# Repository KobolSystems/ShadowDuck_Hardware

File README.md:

# ShadowDuck Hardware

## DRAFT

<!-- Repo Cover Image -->

## Overview
The ShadowDuck is a hardware platform designed for performing keystroke injection attacks. Our goal with this platform is to provide a budget-friendly, educational, and ethical pen-testing tool that resembles a legitimate USB stick, avoiding unnecessary scrutiny. We aim to give newcomers to cybersecurity the opportunity to experiment with these tools and eventually apply their skills in legitimate, professional roles within the industry.

## PCB Render

add renders here

## Technical Specifications
- **PCB Dimensions:** 50mm x 20mm
- **Layers:** 2
- **Material:** FR4
- **Thickness:** 1.6mm
- **Copper Weight:** 1oz (35µm)
- **Surface Finish:** HASL (Lead-Free)
- **Color:** Black Solder Mask with White Silkscreen
- **Connectors:**
  - USB-A Male Connector
  - SWD Programming Header
- **Microcontroller:** RP2040
- **Power Supply:**
  - 5V from USB
  - 3.3V LDO Regulator
- **LED Indicators:**
  - Power LED (Red)
  - Status LED (Green)

## Components
- **Microcontroller:** Raspberry Pi RP2040
- **Memory:** 2MB QSPI Flash
- **Crystal Oscillator:** 12MHz
- **Capacitors:**
  - 10µF (4x)
  - 0.1µF (2x)
- **Resistors:**
  - 10kΩ (2x)
- **LEDs:**
  - Red LED (Power)
  - Green LED (Status)

## Getting Started
### Prerequisites
- [KiCad](https://kicad.org/) (for viewing and editing the PCB design files)
- [PlatformIO](https://platformio.org/) (for firmware development)
- Basic knowledge of PCB design and electronics

### Installation
1. **Clone the repository:**
   ```bash
   git clone https://github.com/KobolSystems/ShadowDuck_Hardware.git
   cd ShadowDuck_Hardware
   ```
**Something about opening in eagle**

## Contributing
We welcome contributions from the community. To contribute:

1. Fork the repository.
2. Create a new branch (`git checkout -b feature-branch`).
3. Make your changes.
4. Commit your changes (`git commit -am 'Add new feature'`).
5. Push to the branch (`git push origin feature-branch`).
6. Open a pull request.

<!-- Licencing Always at the Bottom -->
## Licencing 

**Creative Commons: Attribution - NonCommercial - ShareAlike 4.0 International (CC BY-NC-SA 4.0)**

**You are free to:**

**Share** — copy and redistribute the material in any medium or format

**Adapt** — remix, transform, and build upon the material

**Under the following terms:**

**Attribution** — You must give appropriate credit, provide a link to the license, and indicate if changes were made. You may do so in any reasonable manner, but not in any way that suggests the licensor endorses you or your use.

**NonCommercial** — You may not use the material for commercial purposes.

**ShareAlike** — If you remix, transform, or build upon the material, you must distribute your contributions under the same license as the original.

No additional restrictions — You may not apply legal terms or technological measures that legally restrict others from doing anything the license permits.

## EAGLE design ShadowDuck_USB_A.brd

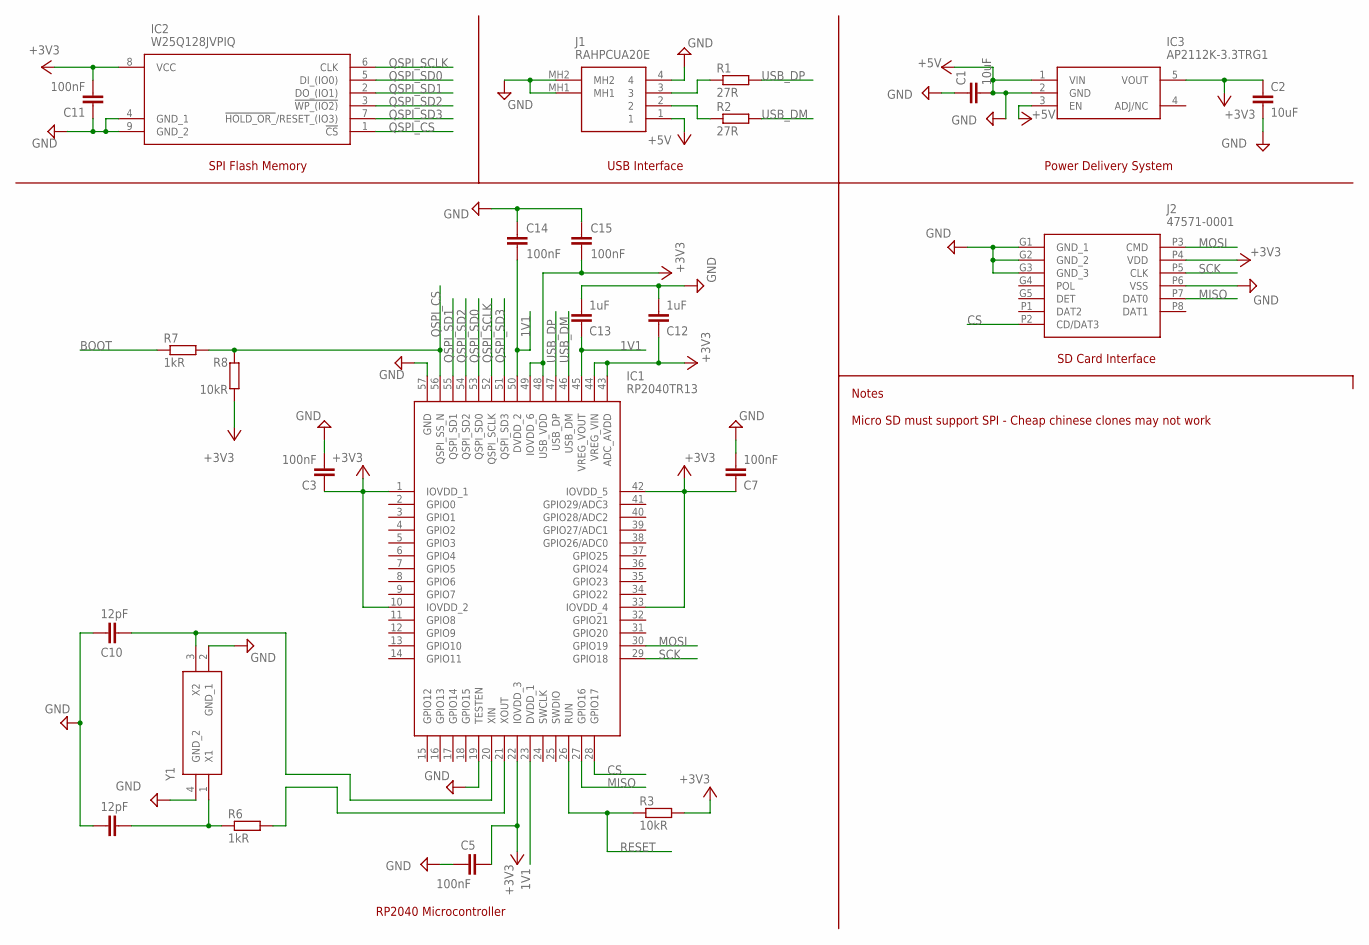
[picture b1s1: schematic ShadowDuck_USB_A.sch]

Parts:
C1, C2: 10uF; C0805K
C3, C5, C7, C11, C14, C15: 100nF; C0402K
C9, C10: 12pF; C0402K
C12, C13: 1uF; C0402K
IC1: RP2040TR13
IC2: W25Q128JVPIQ; SON127P600X500X80-9N
IC3: AP2112K-3.3TRG1; SOT95P282X130-5N
J1: RAHPCUA20E
J2: 47571-0001; 475710001
R1, R2: 27R; R0402
R3, R8: 10kR; R0402
R6, R7: 1kR; R0402
Y1: ABM3BAIG-12.000MHZ-12-4-T; ABM3BAIG

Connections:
1V1: C13.1, C14.2, IC1.23 (DVDD_1), IC1.45 (VREG_VOUT), IC1.50 (DVDD_2)
+3V3: C2.1, C3.1, C5.1, C7.1, C11.2, C12.1, C15.2, IC1.1 (IOVDD_1), IC1.10 (IOVDD_2), IC1.22 (IOVDD_3), IC1.33 (IOVDD_4), IC1.42 (IOVDD_5), IC1.43 (ADC_AVDD), IC1.44 (VREG_VIN), IC1.48 (USB_VDD), IC1.49 (IOVDD_6), IC2.8 (VCC), IC3.5 (VOUT), J2.P4 (VDD), R3.2, R8.1
+5V: C1.2, IC3.1 (VIN), IC3.2 (GND), IC3.3 (EN), J1.1
BOOT: R7.1
CS: IC1.28 (GPIO17), J2.P2 (CD/DAT3)
GND: C1.1, C2.2, C3.2, C5.2, C7.2, C9.1, C10.1, C11.1, C12.2, C13.2, C14.1, C15.1, IC1.19 (TESTEN), IC1.57 (GND), IC2.4 (GND_1), IC2.9 (GND_2), J1.4, J1.MH1, J1.MH2, J2.G1 (GND_1), J2.G2 (GND_2), J2.G3 (GND_3), J2.P6 (VSS), Y1.2 (GND_1), Y1.4 (GND_2)
MISO: IC1.27 (GPIO16), J2.P7 (DAT0)
MOSI: IC1.30 (GPIO19), J2.P3 (CMD)
unnamed: C10.2, IC1.20 (XIN), Y1.3 (X2)
unnamed: IC1.21 (XOUT), R6.2
unnamed: J1.3, R1.1
unnamed: C9.2, R6.1, Y1.1 (X1)
unnamed: J1.2, R2.1
QSPI_CS: IC1.56 (QSPI_SS_N), IC2.1 (!CS), R7.2, R8.2
QSPI_SCLK: IC1.52 (QSPI_SCLK), IC2.6 (CLK)
QSPI_SD0: IC1.53 (QSPI_SD0), IC2.5 (DI_(IO0))
QSPI_SD1: IC1.55 (QSPI_SD1), IC2.2 (DO_(IO1))
QSPI_SD2: IC1.54 (QSPI_SD2), IC2.3 (!WP_(IO2))
QSPI_SD3: IC1.51 (QSPI_SD3), IC2.7 (!HOLD_OR_!/RESET_(IO3))
RESET: IC1.26 (RUN), R3.1
SCK: IC1.29 (GPIO18), J2.P5 (CLK)
USB_DM: IC1.46 (USB_DM), R2.2
USB_DP: IC1.47 (USB_DP), R1.2

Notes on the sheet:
SPI Flash Memory
RP2040 Microcontroller
Power Delivery System
USB Interface
SD Card Interface
Notes Micro SD must support SPI - Cheap chinese clones may not work

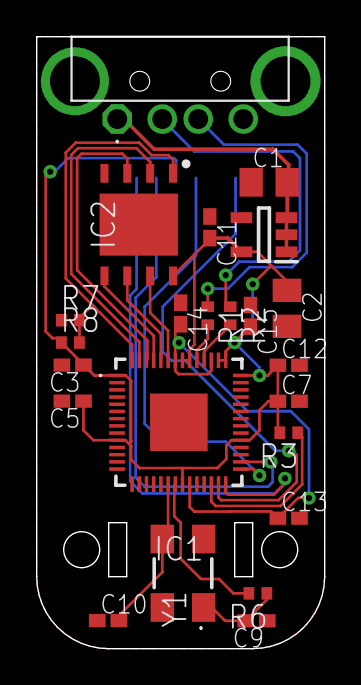
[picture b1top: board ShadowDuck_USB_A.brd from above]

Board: 2 copper layers, 16.0 x 34.0 mm, 24 parts (1 on the bottom side), 22 nets.

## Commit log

2024-09-09 DRC Check

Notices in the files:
README.md:
License: CC-BY-NC-SA-4.0
